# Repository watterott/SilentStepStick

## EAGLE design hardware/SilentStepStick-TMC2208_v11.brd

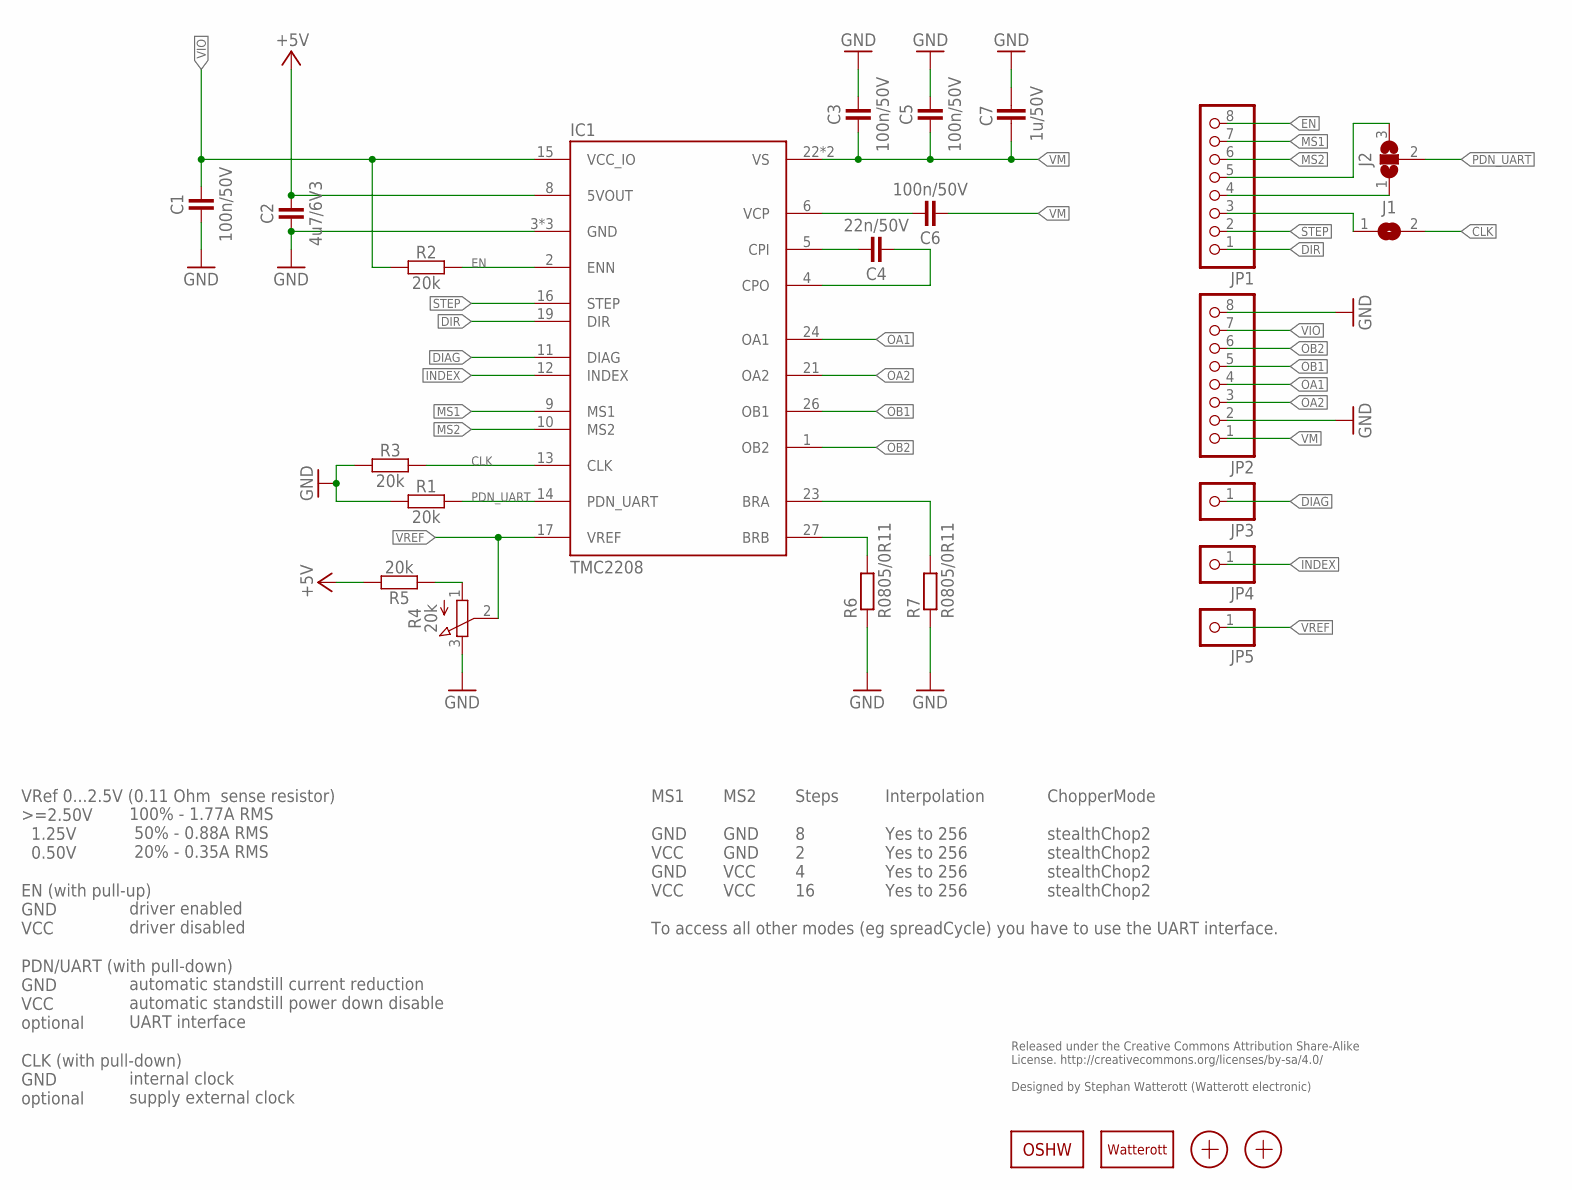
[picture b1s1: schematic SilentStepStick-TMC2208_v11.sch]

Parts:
C1, C3, C5, C6: 100n/50V; C0402
C2: 4u7/6V3; C0402
C4: 22n/50V; C0402
C7: 1u/50V; C0805
IC1: TMC2208; QFN28-PAD
J1: JUMPER2-0402
J2: JUMPER3-0402-NC; JUMPER3-0402_NC
JP1, JP2: PINHD-1X08_2.54-S; 1X08-S
JP3, JP4, JP5: PINHD-1X1; 1X01
LOGO1: OSHW_LOGOX0070; OSHW_6X70
LOGO2: LOGO-S_PLACE_M; SPARK_TPLACE_M
R1, R2, R3, R5: 20k; C0402
R4: 20k; POT_EVM3R
R6, R7: R0805/0R11; M0805
X1, X2: PASSER-04; PASSER_04MM

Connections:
+5V: C2.2, IC1.8 (5VOUT), R5.2
BRA: IC1.23 (BRA), R7.2
BRB: IC1.27 (BRB), R6.2
CLK: IC1.13 (CLK), J1.2, R3.2
CPI: C4.2, IC1.5 (CPI)
CPO: C4.1, IC1.4 (CPO)
DIAG: IC1.11 (DIAG), JP3.1
DIR: IC1.19 (DIR), JP1.1
EN: IC1.2 (ENN), JP1.8, R2.2
GND: C1.1, C2.1, C3.2, C5.2, C7.2, IC1.3 (GND), IC1.18 (GND), IC1.TP (GND), JP2.2, JP2.8, R1.1, R3.1, R4.3 (E), R6.1, R7.1
INDEX: IC1.12 (INDEX), JP4.1
MS1: IC1.9 (MS1), JP1.7
MS2: IC1.10 (MS2), JP1.6
unnamed: J2.3, JP1.5
unnamed: J1.1, JP1.3
unnamed: J2.1, JP1.4
OA1: IC1.24 (OA1), JP2.4
OA2: IC1.21 (OA2), JP2.3
OB1: IC1.26 (OB1), JP2.5
OB2: IC1.1 (OB2), JP2.6
PDN_UART: IC1.14 (PDN_UART), J2.2, R1.2
STEP: IC1.16 (STEP), JP1.2
VCP: C6.2, IC1.6 (VCP)
VIO: C1.2, IC1.15 (VCC_IO), JP2.7, R2.1
VM: C3.1, C5.1, C6.1, C7.1, IC1.22 (VS), IC1.28 (VS), JP2.1
VREF: IC1.17 (VREF), JP5.1, R4.2 (S)
VREF1: R4.1 (A), R5.1

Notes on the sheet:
Released under the Creative Commons Attribution Share-Alike License. http://creativecommons.org/licenses/by-sa/4.0/ Designed by Stephan Watterott (Watterott electronic)
VRef 0...2.5V (0.11 Ohm sense resistor) >=2.50V 1.25V 0.50V EN (with pull-up) GND VCC PDN/UART (with pull-down) GND VCC optional CLK (with pull-down) GND optional
100% - 1.77A RMS 50% - 0.88A RMS 20% - 0.35A RMS driver enabled driver disabled automatic standstill current reduction automatic standstill power down disable UART interface internal clock supply external clock
MS1 GND VCC GND VCC To access all other modes (eg spreadCycle) you have to use the UART interface.
MS2 GND GND VCC VCC
Steps 8 2 4 16
Interpolation Yes to 256 Yes to 256 Yes to 256 Yes to 256
ChopperMode stealthChop2 stealthChop2 stealthChop2 stealthChop2

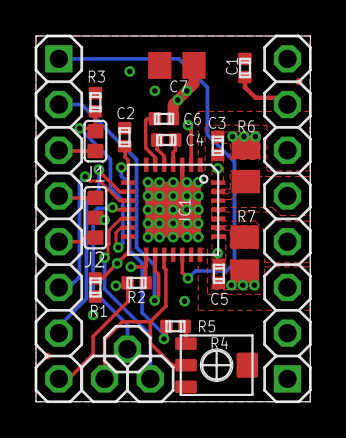
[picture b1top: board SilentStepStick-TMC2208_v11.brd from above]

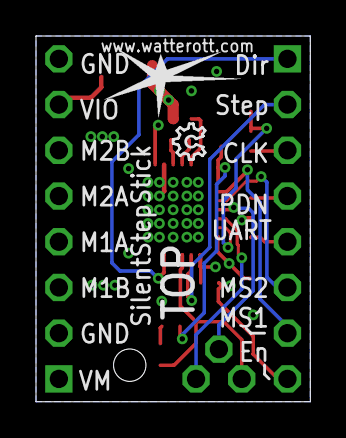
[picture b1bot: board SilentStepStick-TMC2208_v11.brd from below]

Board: 4 copper layers, 15.2 x 20.3 mm, 26 parts (2 on the bottom side), 27 nets.

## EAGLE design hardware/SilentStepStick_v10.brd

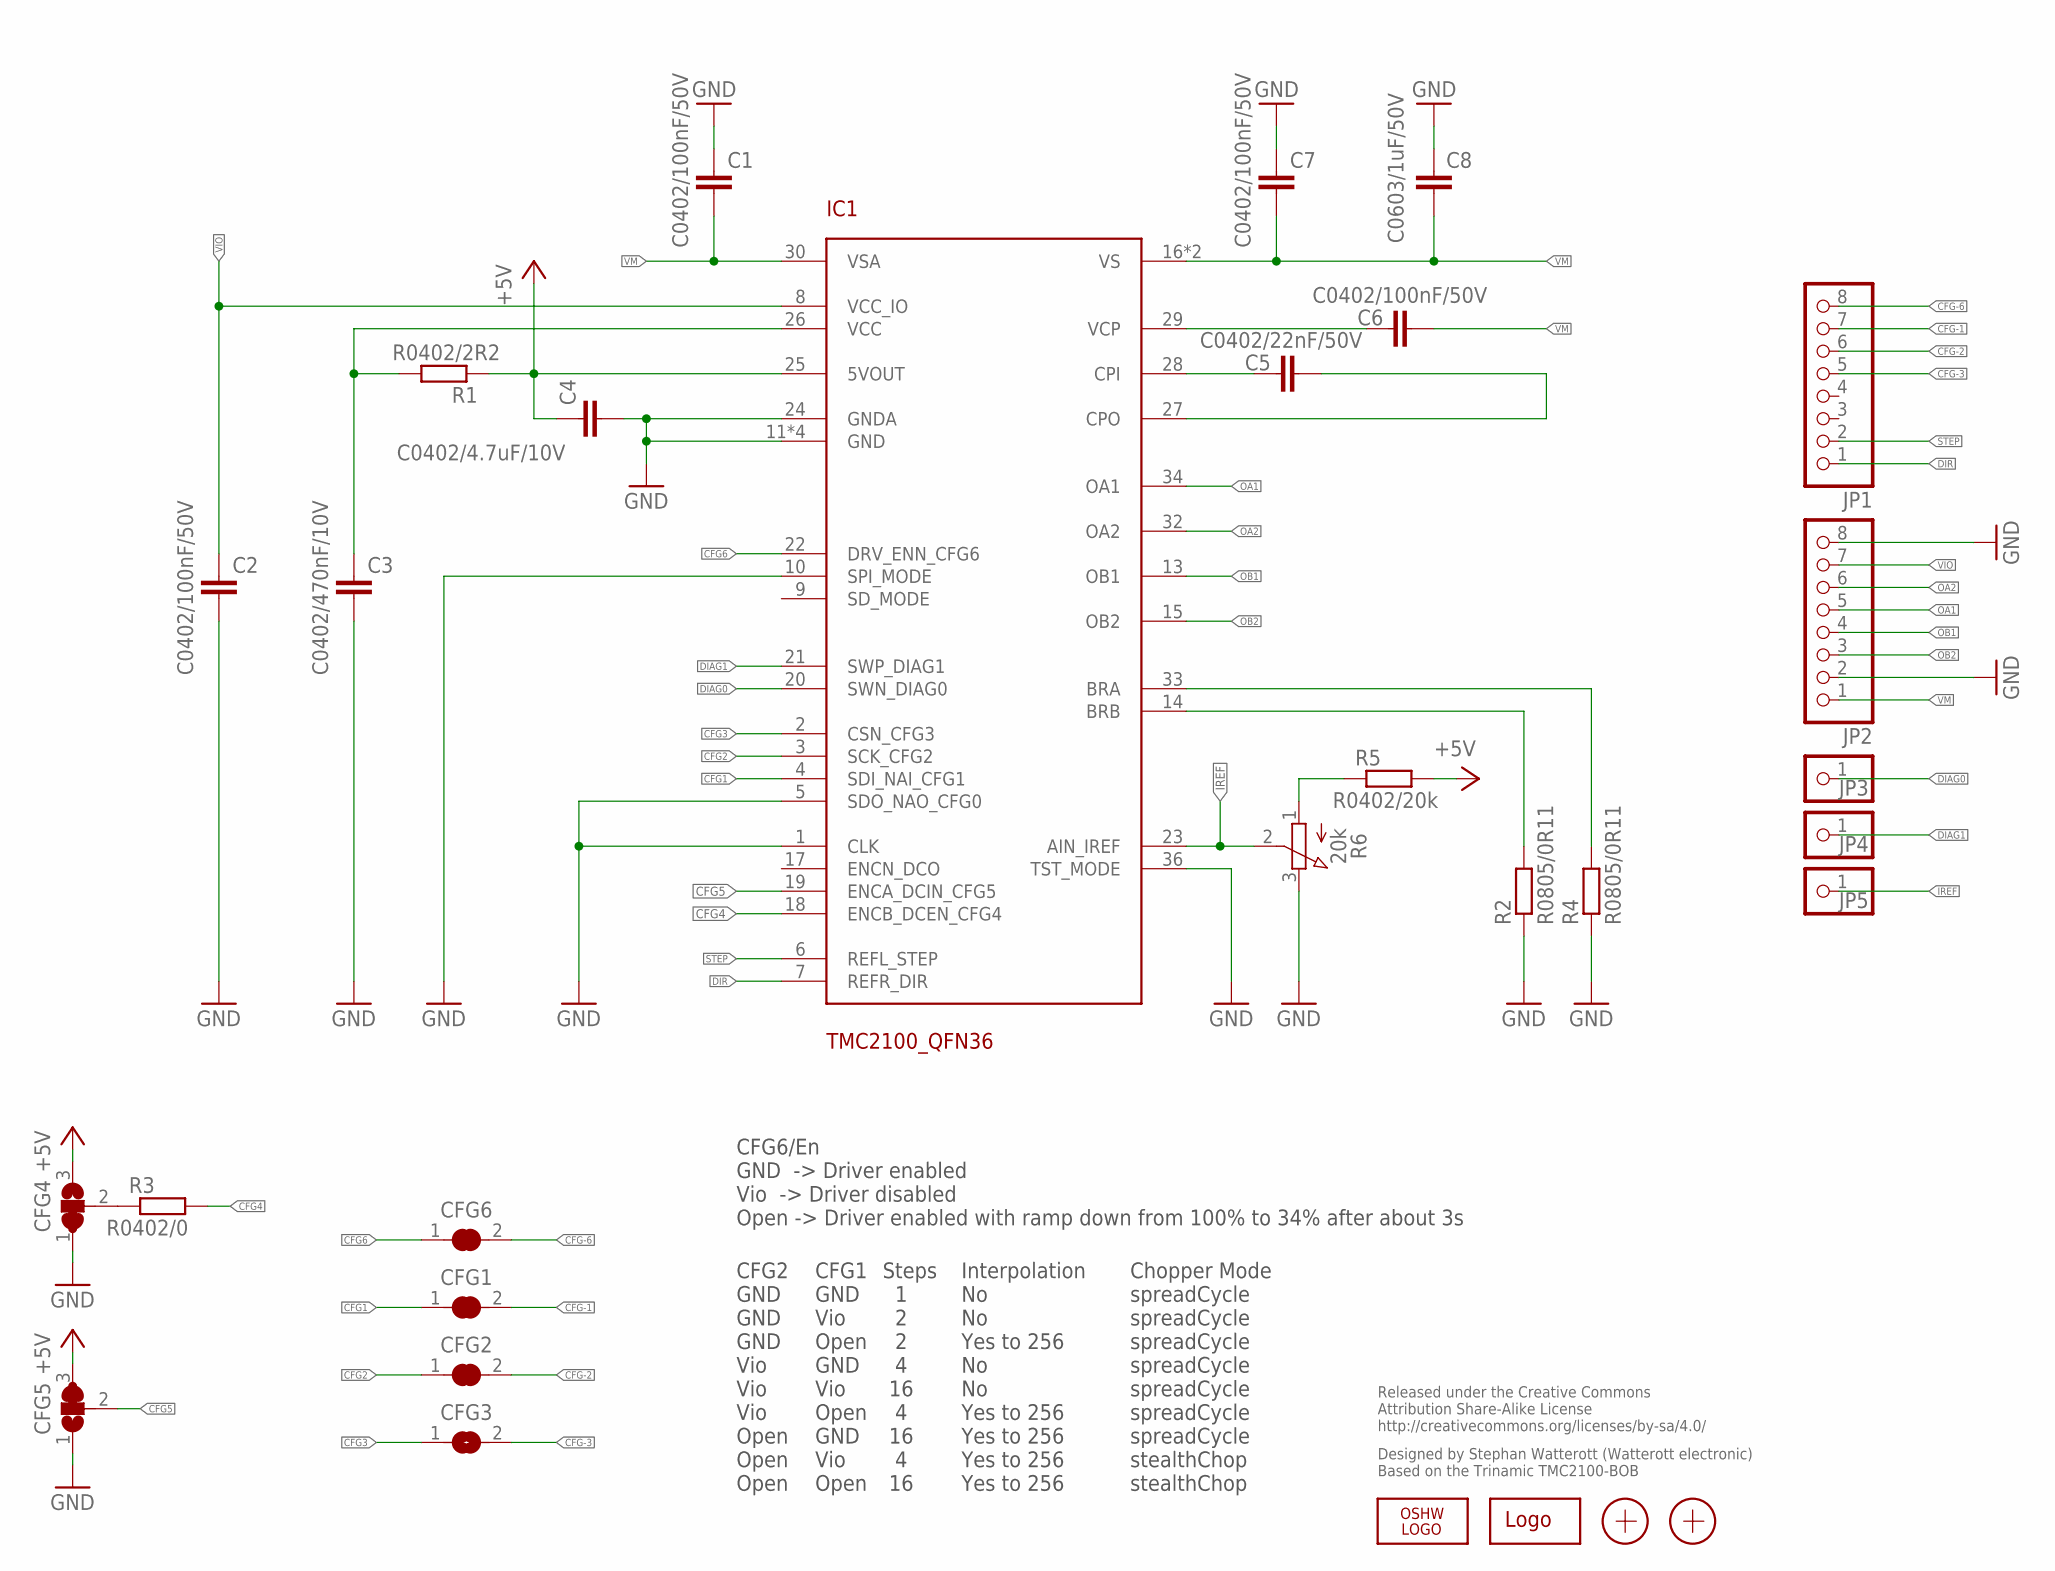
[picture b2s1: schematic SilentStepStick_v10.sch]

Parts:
C1, C2, C6, C7: C0402/100nF/50V; C0402
C3: C0402/470nF/10V; C0402
C4: C0402/4.7uF/10V; C0402
C5: C0402/22nF/50V; C0402
C8: C0603/1uF/50V; C0603
CFG1, CFG2, CFG3, CFG6: JUMPER2-0201
CFG4: JUMPER3-0201-NC; JUMPER3-0201_NC
CFG5: JUMPER3-0201
IC1: TMC2100_QFN36; QFN36
JP1, JP2: PINHD-1X08_2.54-S; 1X08-S
JP3, JP4, JP5: PINHD-1X1; 1X01
LOGO1: OSHW_LOGOX0070; OSHW_6X70
LOGO2: LOGO-S_PLACE_M; SPARK_TPLACE_M
R1: R0402/2R2; R0402
R2, R4: R0805/0R11; M0805
R3: R0402/0; R0402
R5: R0402/20k; R0402
R6: 20k; POT_EVM3R
X1, X2: PASSER-07; PASSER_07MM

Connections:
+5V: C4.1, CFG4.3, CFG5.3, IC1.25 (5VOUT), R1.1, R5.2
CFG1: CFG1.1, IC1.4 (SDI_NAI_CFG1)
CFG2: CFG2.1, IC1.3 (SCK_CFG2)
CFG3: CFG3.1, IC1.2 (CSN_CFG3)
CFG4: IC1.18 (ENCB_DCEN_CFG4), R3.2
CFG5: CFG5.2, IC1.19 (ENCA_DCIN_CFG5)
CFG6: CFG6.1, IC1.22 (DRV_ENN_CFG6)
CFG-1: CFG1.2, JP1.7
CFG-2: CFG2.2, JP1.6
CFG-3: CFG3.2, JP1.5
CFG-6: CFG6.2, JP1.8
CPI: C5.1, IC1.28 (CPI)
CPO: C5.2, IC1.27 (CPO)
DIAG0: IC1.20 (SWN_DIAG0), JP3.1
DIAG1: IC1.21 (SWP_DIAG1), JP4.1
DIR: IC1.7 (REFR_DIR), JP1.1
GND: C1.1, C2.2, C3.2, C4.2, C7.1, C8.2, CFG4.1, CFG5.1, IC1.1 (CLK), IC1.5 (SDO_NAO_CFG0), IC1.10 (SPI_MODE), IC1.11 (GND), IC1.12 (GND), IC1.24 (GNDA), IC1.35 (GND), IC1.36 (TST_MODE), IC1.GND_PAD (GND), JP2.2, JP2.8, R2.1, R4.1, R6.3 (E)
IREF: IC1.23 (AIN_IREF), JP5.1, R6.2 (S)
unnamed: CFG4.2, R3.1
unnamed: IC1.33 (BRA), R4.2
unnamed: IC1.14 (BRB), R2.2
OA1: IC1.34 (OA1), JP2.5
OA2: IC1.32 (OA2), JP2.6
OB1: IC1.13 (OB1), JP2.4
OB2: IC1.15 (OB2), JP2.3
STEP: IC1.6 (REFL_STEP), JP1.2
VCC: C3.1, IC1.26 (VCC), R1.2
VCP: C6.1, IC1.29 (VCP)
VIO: C2.1, IC1.8 (VCC_IO), JP2.7
VM: C1.2, C6.2, C7.2, C8.1, IC1.16 (VS), IC1.30 (VSA), IC1.31 (VS), JP2.1
VREF1: R5.1, R6.1 (A)

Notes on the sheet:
Released under the Creative Commons Attribution Share-Alike License http://creativecommons.org/licenses/by-sa/4.0/
Designed by Stephan Watterott (Watterott electronic) Based on the Trinamic TMC2100-BOB
CFG6/En GND -> Driver enabled Vio -> Driver disabled Open -> Driver enabled with ramp down from 100% to 34% after about 3s
CFG2 GND GND GND Vio Vio Vio Open Open Open
CFG1 GND Vio Open GND Vio Open GND Vio Open
Steps 1 2 2 4 16 4 16 4 16
Interpolation No No Yes to 256 No No Yes to 256 Yes to 256 Yes to 256 Yes to 256
Chopper Mode spreadCycle spreadCycle spreadCycle spreadCycle spreadCycle spreadCycle spreadCycle stealthChop stealthChop

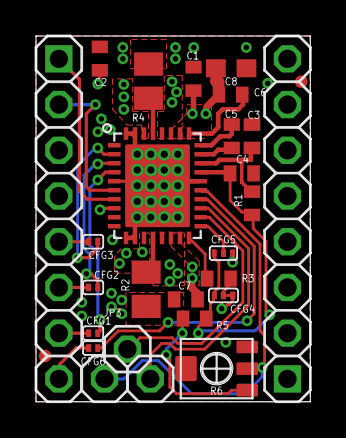
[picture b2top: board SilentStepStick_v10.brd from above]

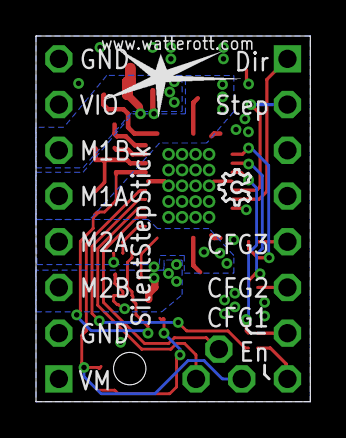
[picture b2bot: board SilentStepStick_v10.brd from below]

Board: 4 copper layers, 15.2 x 20.3 mm, 30 parts (2 on the bottom side), 31 nets.

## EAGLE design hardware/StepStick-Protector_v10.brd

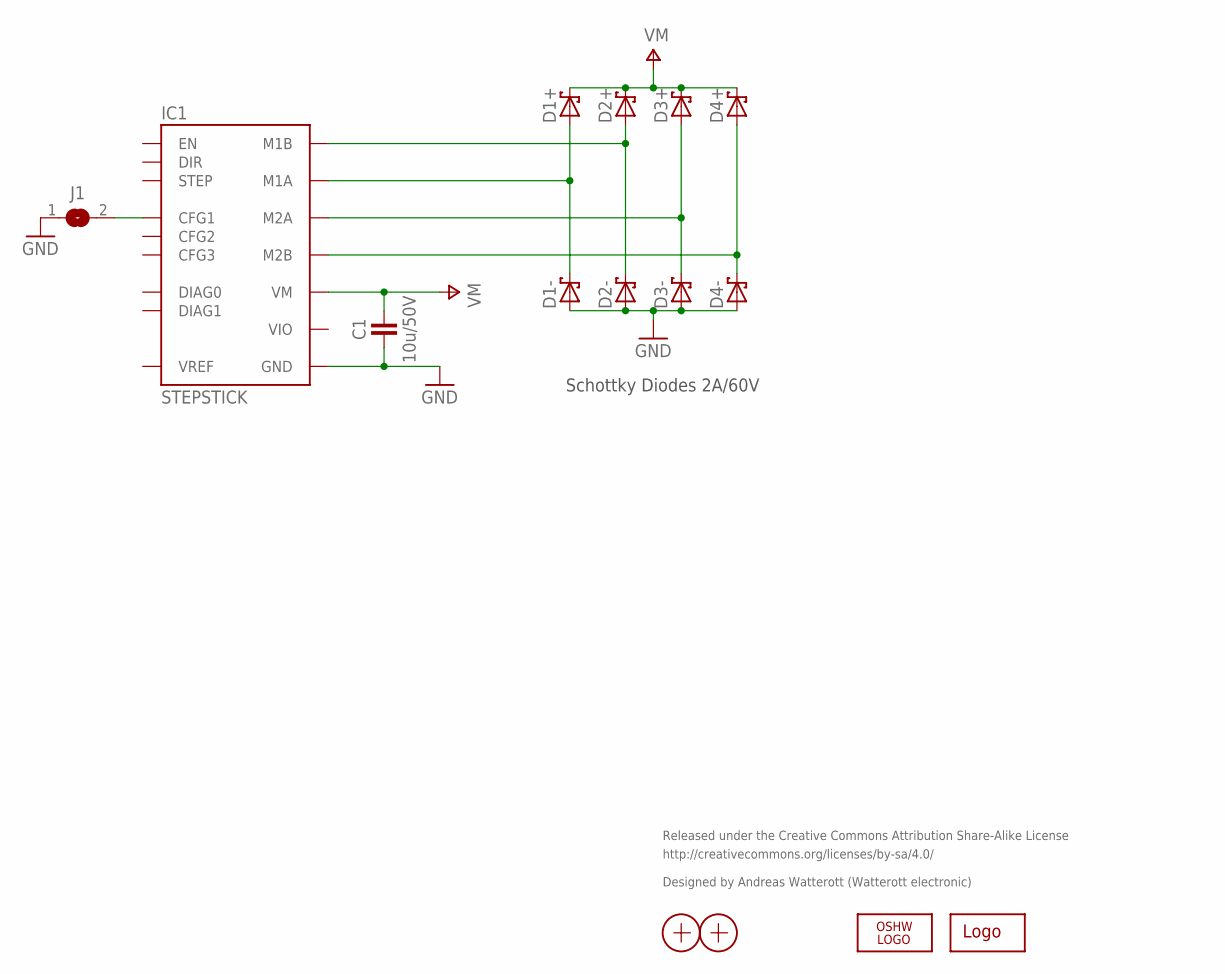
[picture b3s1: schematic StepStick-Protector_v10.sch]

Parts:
C1: 10u/50V; C1210
D1+, D1-, D2+, D2-, D3+, D3-, D4+, D4-: D_SCHOTTKY-SS14; SMA_DO214AC
IC1: STEPSTICK
J1: JUMPER2-0603-NC; JUMPER2-0603_NC
LOGO1: OSHW_LOGOX0070; OSHW_6X70
LOGO2: LOGO-S_PLACE_S; SPARK_TPLACE_S
X1, X2: PASSER

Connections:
GND: C1.1, D1-.A, D2-.A, D3-.A, D4-.A, IC1.GND@1 (GND), IC1.GND@2 (GND), J1.1
M1A: D1+.A, D1-.C, IC1.M1A
M1B: D2+.A, D2-.C, IC1.M1B
M2A: D3+.A, D3-.C, IC1.M2A
M2B: D4+.A, D4-.C, IC1.M2B
unnamed: IC1.CFG1, J1.2
VIO: IC1.VIO
VM: C1.2, D1+.C, D2+.C, D3+.C, D4+.C, IC1.VM

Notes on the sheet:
Released under the Creative Commons Attribution Share-Alike License
http://creativecommons.org/licenses/by-sa/4.0/
Designed by Andreas Watterott (Watterott electronic)
Schottky Diodes 2A/60V

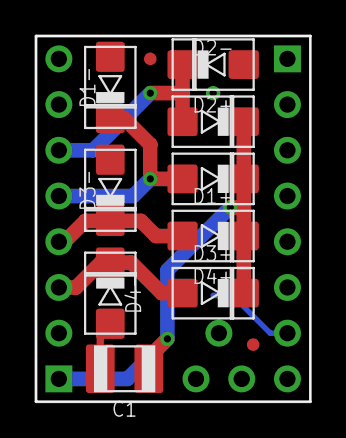
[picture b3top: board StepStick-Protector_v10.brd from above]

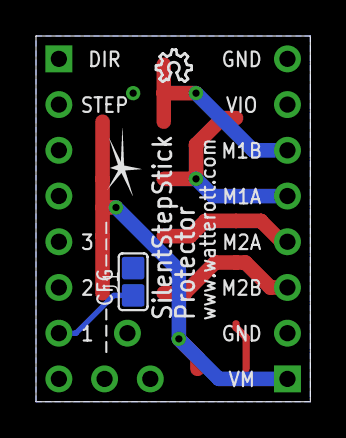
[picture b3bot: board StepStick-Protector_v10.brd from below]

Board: 2 copper layers, 15.2 x 20.3 mm, 15 parts (3 on the bottom side), 7 nets.

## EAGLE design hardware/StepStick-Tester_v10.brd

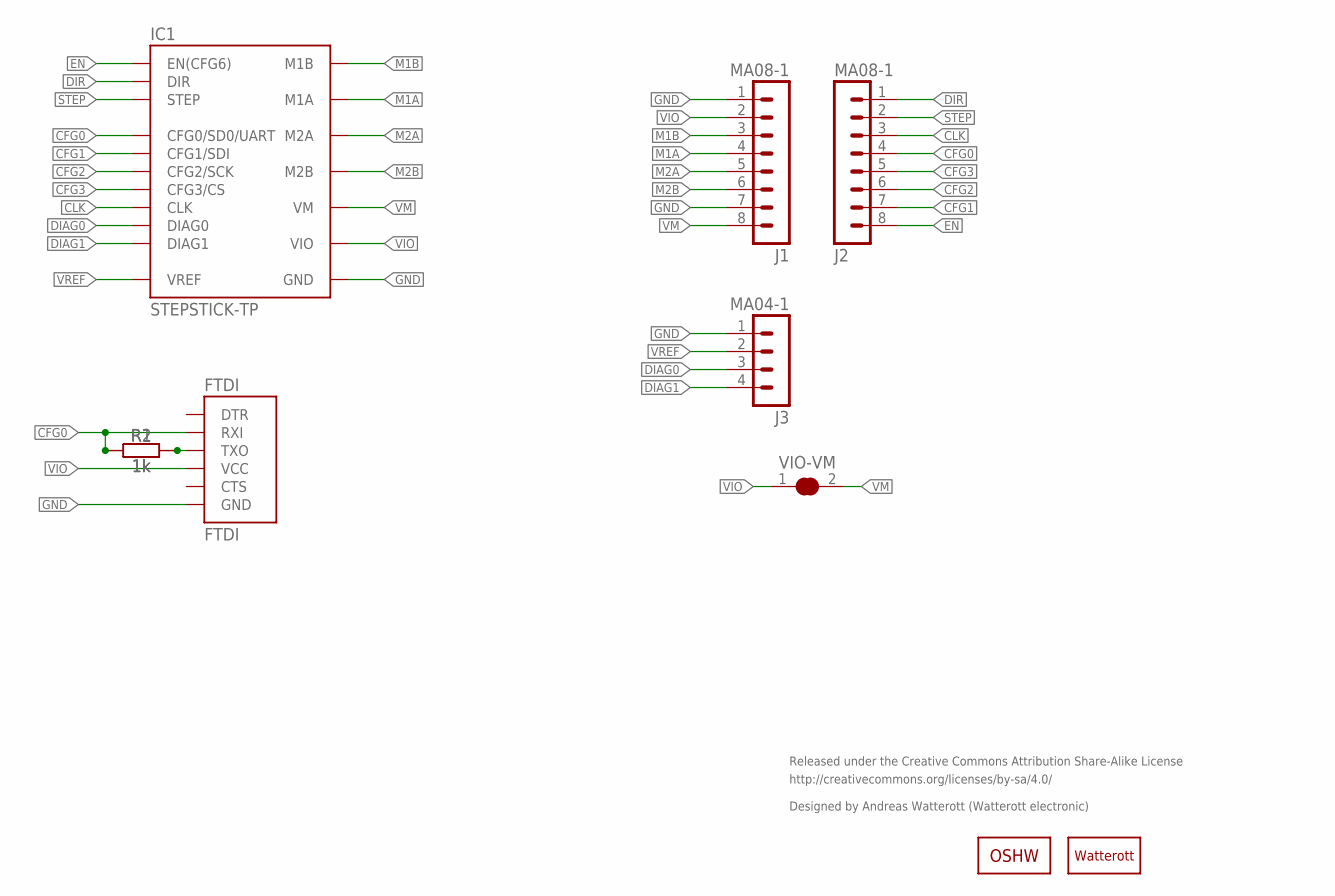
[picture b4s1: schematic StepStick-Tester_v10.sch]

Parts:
FTDI: FTDI
IC1: STEPSTICK-TP; STEPSTICK_TP
J1, J2: MA08-1
J3: MA04-1
LOGO1: OSHW_LOGOX0070; OSHW_6X70
LOGO2: LOGO-S_PLACE_S; SPARK_TPLACE_S
R1: 1k; R0207/7
R2: 1k; C0805
VIO-VM: JUMPER2-0603-NC; JUMPER2-0603_NC

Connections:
CFG0: FTDI.5-RXI (RXI), IC1.NC/CFG0 (CFG0/SD0/UART), J2.4, R1.1, R2.1
CFG1: IC1.CFG1 (CFG1/SDI), J2.7
CFG2: IC1.CFG2 (CFG2/SCK), J2.6
CFG3: IC1.CFG3 (CFG3/CS), J2.5
CLK: IC1.NC/CLK (CLK), J2.3
DIAG0: IC1.DIAG0, J3.3
DIAG1: IC1.DIAG1, J3.4
DIR: IC1.DIR, J2.1
EN: IC1.EN (EN(CFG6)), J2.8
GND: FTDI.1-GND (GND), IC1.GND@1 (GND), IC1.GND@2 (GND), J1.1, J1.7, J3.1
M1A: IC1.M1A, J1.4
M1B: IC1.M1B, J1.3
M2A: IC1.M2A, J1.5
M2B: IC1.M2B, J1.6
STEP: IC1.STEP, J2.2
TX: FTDI.4-TXO (TXO), R1.2, R2.2
VIO: FTDI.3-VCC (VCC), IC1.VIO, J1.2, VIO-VM.1
VM: IC1.VM, J1.8, VIO-VM.2
VREF: IC1.VREF, J3.2

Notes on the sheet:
Released under the Creative Commons Attribution Share-Alike License
http://creativecommons.org/licenses/by-sa/4.0/
Designed by Andreas Watterott (Watterott electronic)

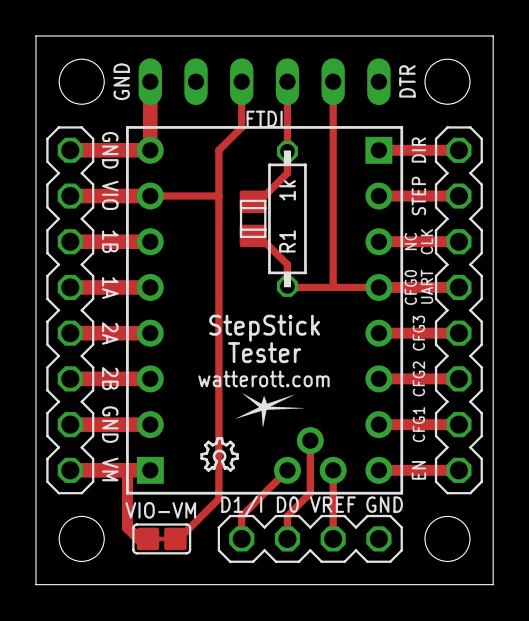
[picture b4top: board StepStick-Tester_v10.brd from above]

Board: 2 copper layers, 25.4 x 30.5 mm, 10 parts (0 on the bottom side), 19 nets.
